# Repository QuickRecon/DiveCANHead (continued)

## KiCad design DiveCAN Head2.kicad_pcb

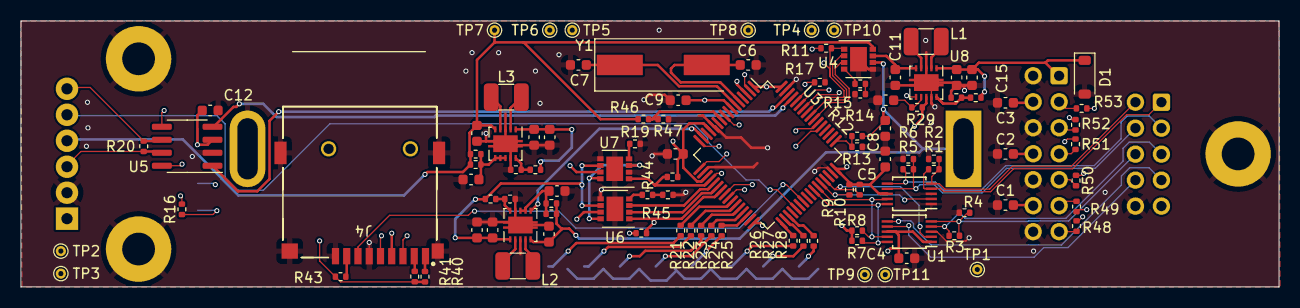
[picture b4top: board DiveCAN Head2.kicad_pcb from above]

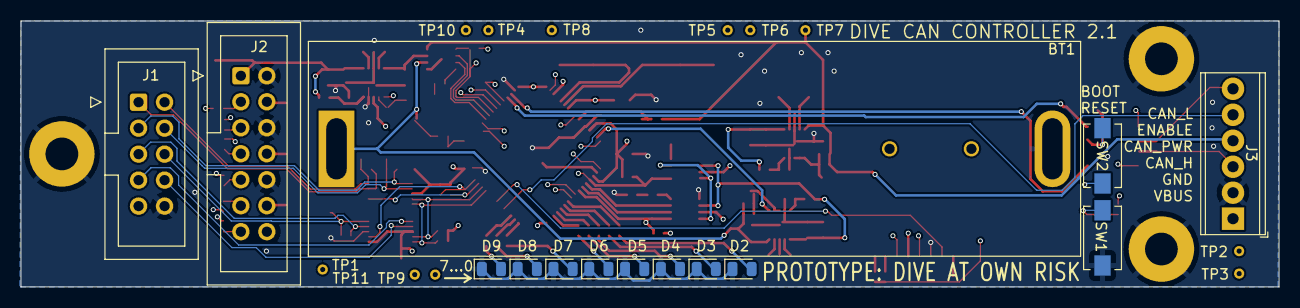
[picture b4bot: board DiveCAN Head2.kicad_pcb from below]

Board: 4 copper layers, 123.0 x 26.0 mm, 120 parts (14 on the bottom side), 94 nets.

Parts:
BT1: Battery_Cell; BatteryHolder_MPD_BH-18650-PC2
C1, C2, C3, C4, C5, C9, C10, C12, C13, C16, C19: 100n; C_0603_1608Metric
C6, C7: 20p; C_0603_1608Metric
C8, C11, C14, C15, C17, C18, C20, C21, C22, C23: 10u; C_0603_1608Metric
D1: MBR0520; D_SOD-123
D2, D3, D4, D5, D6, D7, D8, D9: LED; LED_0805_2012Metric
H1, H2, H4: MountingHole_Pad; MountingHole_3.2mm_M3_Pad
J1: Analog Connection; IDC-Header_2x05_P2.54mm_Vertical
J2: Digital Connection; IDC-Header_2x07_P2.54mm_Vertical
J3: Conn_01x06_Pin; TerminalBlock_Phoenix_MPT-0,5-6-2.54_1x06_P2.54mm_Horizontal
J4: Micro_SD_Card; CONN9_0185-02_GSW
L1, L2, L3: 2.2u; L_4x4
R1, R3, R5, R7, R8, R9, R10, R11, R12, R13, R16, R17, R18, R21, R22, R23, R24, R25, R26, R27, R28, R40, R41, R43, R45, R46, R47: 10k; R_0402_1005Metric
R2, R4, R6, R14, R15, R29, R32, R33, R36, R37, R42, R44: 200; R_0402_1005Metric
R19, R48, R49, R50, R51, R52, R53: 800; R_0402_1005Metric
R20: 560; R_0402_1005Metric
R30, R34, R38: 1M; R_0402_1005Metric
R31: 100k; R_0402_1005Metric
R35, R39: 178k; R_0402_1005Metric
SW1, SW2: RST; SW_SPST_EVQPE1
TP1: BATTERY; TestPoint_THTPad_D1.0mm_Drill0.5mm
TP2: VCC; TestPoint_THTPad_D1.0mm_Drill0.5mm
TP3: VBUS; TestPoint_THTPad_D1.0mm_Drill0.5mm
TP4: SOL_EN; TestPoint_THTPad_D1.0mm_Drill0.5mm
TP5: BAT_REG; TestPoint_THTPad_D1.0mm_Drill0.5mm
TP6: CAN_REG; TestPoint_THTPad_D1.0mm_Drill0.5mm
TP7: CAN_PWR; TestPoint_THTPad_D1.0mm_Drill0.5mm
TP8: BAT_EN; TestPoint_THTPad_D1.0mm_Drill0.5mm
TP9: BUS_STAT; TestPoint_THTPad_D1.0mm_Drill0.5mm
TP10: SOL_STAT; TestPoint_THTPad_D1.0mm_Drill0.5mm
TP11: VCC_STAT; TestPoint_THTPad_D1.0mm_Drill0.5mm
U1, U2: ADS1115IDGS; TSSOP-10_3x3mm_P0.5mm
U3: STM32L431RCTx; LQFP-64_10x10mm_P0.5mm
U4, U6, U7: TPS2115; VSON-8_3.3x3.3mm_P0.65mm_NexFET
U5: TCAN33X; SOIC-8_3.9x4.9mm_P1.27mm
U8, U9, U10: TPS63000; Texas_DRC0010J
Y1: 8MHz; Crystal_SMD_HC49-SD

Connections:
/ALRT_ADC1: R9.2, U2.2 (ALERT/RDY), U3.44 (PA11)
/ALRT_ADC2: R10.2, U1.2 (ALERT/RDY), U3.45 (PA12)
/AUX+: J1.7, U1.6 (AIN2)
/AUX-: J1.8, U1.7 (AIN3)
/BATTERY: BT1.1 (+), C8.2, C22.1, R12.2, R32.2, R33.2, TP1.1, U4.6 (IN2), U9.5 (VIN)
/BATTERY_EN: TP8.1, U3.15 (PA1), U9.6 (EN)
/BATTERY_REGULATED: C17.1, C18.1, R34.1, TP5.1, U6.6 (IN2), U7.6 (IN2), U9.1 (VOUT)
/BOOT: R17.2, SW2.1 (A), U3.60 (PH3)
/BUS_SEL1: U3.22 (PA6), U6.2 (D0)
/BUS_SEL2: U3.21 (PA5), U6.3 (D1)
/BUS_STAT: R45.2, TP9.1, U3.23 (PA7), U6.1 (STAT)
/C1+: J1.1, R1.1, U2.4 (AIN0)
/C1-: J1.2, R1.2, R2.1, U2.5 (AIN1)
/C2+: J1.3, R5.1, U2.6 (AIN2)
/C2-: J1.4, R5.2, R6.1, U2.7 (AIN3)
/C3+: J1.5, R3.1, U1.4 (AIN0)
/C3-: J1.6, R3.2, R4.1, U1.5 (AIN1)
/CAN_PWR: C23.1, J3.4, R36.2, R37.2, R46.2, TP7.1, U4.8 (IN1), U10.5 (VIN)
/CAN_REGULATED: C20.1, C21.1, R38.1, TP6.1, U6.8 (IN1), U7.3 (D1), U7.8 (IN1), U10.1 (VOUT)
/CAN_SHDN: U3.3 (PC14), U5.5 (SHDN)
/CAN_SILENT: U3.2 (PC13), U5.8 (S)
/LED_0: R21.2, U3.26 (PB0)
/LED_1: R22.2, U3.27 (PB1)
/LED_2: R23.2, U3.28 (PB2)
/LED_3: R24.2, U3.29 (PB10)
/LED_4: R25.2, U3.30 (PB11)
/LED_5: R26.2, U3.33 (PB12)
/LED_6: R27.2, U3.34 (PB13)
/LED_7: R28.2, U3.35 (PB14)
/RST: C9.2, R16.1, SW1.2 (B), U3.7 (NRST)
/SCL: R7.2, U1.10 (SCL), U2.10 (SCL), U3.42 (PA9)
/SDA: R8.2, U1.9 (SDA), U2.9 (SDA), U3.43 (PA10)
/SD_CLK: J4.5 (CLK), U3.53 (PC12)
/SD_CMD: J4.3 (CMD), U3.54 (PD2)
/SD_DAT0: J4.7 (DAT0), U3.39 (PC8)
/SOLENOID: TP4.1, U3.9 (PC1), U8.6 (EN)
/SOL_OUT: C14.1, C15.1, D1.1 (K), J2.1, R30.1, U8.1 (VOUT)
/SOL_SEL1: U3.56 (PB4), U4.2 (D0)
/SOL_SEL2: U3.55 (PB3), U4.3 (D1)
/SOL_STAT: R11.2, TP10.1, U3.57 (PB5), U4.1 (STAT)
/SSC1_RX: R52.1, U3.59 (PB7)
/SSC1_TX: R53.1, U3.58 (PB6)
/SSC2_RX: R50.1, U3.16 (PA2)
/SSC2_TX: R51.1, U3.17 (PA3)
/SSC3_RX: R48.1, U3.24 (PC4)
/SSC3_TX: R49.1, U3.25 (PC5)
/Solenoid Driver/IN: C11.2, U4.7 (OUT), U8.5 (VIN)
/VCC_STAT: R18.2, TP11.1, U3.20 (PA4), U7.1 (STAT)
/~CAN_EN: J3.5, U3.37 (PC6)
GNDREF: BT1.2 (-), C1.1, C2.1, C3.1, C4.2, C5.2, C6.1, C7.1, C8.1, C9.1, C10.2, C11.1, C12.2, C13.1, C14.2, C15.2, C16.1, C17.2, C18.2, C19.1, C20.2, C21.2, C22.2, C23.2, D1.2 (A), D2.1 (K), D3.1 (K), D4.1 (K), D5.1 (K), D6.1 (K), D7.1 (K), D8.1 (K), D9.1 (K), H1.1, H2.1, H4.1, J1.10, J2.2, J2.6, J2.10, J2.14, J3.2, J4.6 (VSS), J4.9 (SHIELD), R2.2, R4.2, R6.2, R13.1, R14.1, R17.1, R19.2, R31.2, R35.2, R39.2, R42.1, R47.1, SW1.1 (A), U1.3 (GND), U2.1 (ADDR), U2.3 (GND), U3.12 (VSSA), U3.18 (VSS), U3.31 (VSS), U3.47 (VSS), U3.63 (VSS), U4.5 (GND), U5.2 (GND), U6.5 (GND), U7.2 (D0), U7.5 (GND), U8.3 (PGND), U8.9 (GND), U8.11 (PGND), U9.3 (PGND), U9.9 (GND), U9.11 (PGND), U10.3 (PGND), U10.9 (GND), U10.11 (PGND)
unnamed: D2.2 (A), R21.1
unnamed: D3.2 (A), R22.1
unnamed: D4.2 (A), R23.1
unnamed: D5.2 (A), R24.1
unnamed: D6.2 (A), R25.1
unnamed: D7.2 (A), R26.1
unnamed: D8.2 (A), R27.1
unnamed: D9.2 (A), R28.1
unnamed: J2.3, R53.2
unnamed: J2.5, R52.2
unnamed: J2.7, R51.2
unnamed: J2.9, R50.2
unnamed: J2.11, R49.2
unnamed: J2.13, R48.2
unnamed: J3.3, R20.1, U5.7 (CANH)
unnamed: J3.6, R20.2, U5.6 (CANL)
unnamed: J4.8 (DAT1), R43.1
unnamed: J4.1 (DAT2), R40.1
unnamed: J4.2 (DAT3/CD), R41.1
unnamed: R14.2, R15.1
unnamed: R42.2, R44.1
unnamed: R12.1, R13.2, U3.49 (PA14)
unnamed: U3.61 (PB8), U5.4 (RXD)
unnamed: U3.62 (PB9), U5.1 (TXD)
unnamed: R46.1, R47.2, U3.10 (PC2)
unnamed: C6.2, U3.5 (PH0), Y1.2
unnamed: C7.2, U3.6 (PH1), Y1.1
unnamed: R15.2, U4.4 (I_LIM)
unnamed: R44.2, U6.4 (I_LIM)
unnamed: R19.1, U7.4 (I_LIM)
unnamed: R30.2, R31.1, U8.10 (FB)
unnamed: L1.2, U8.4 (L1)
unnamed: L1.1, U8.2 (L2)
unnamed: C13.2, R29.2, U8.7 (PS/SYNC)
unnamed: R34.2, R35.1, U9.10 (FB)
unnamed: L2.2, U9.4 (L1)
unnamed: L2.1, U9.2 (L2)
unnamed: C16.2, R32.1, R33.1, U9.7 (PS/SYNC), U9.8 (VINA)
unnamed: C19.2, R36.1, R37.1, U10.6 (EN), U10.7 (PS/SYNC), U10.8 (VINA)
unnamed: R38.2, R39.1, U10.10 (FB)
unnamed: L3.2, U10.4 (L1)
unnamed: L3.1, U10.2 (L2)
VBUS: C1.2, C2.2, C3.2, J1.9, J2.4, J2.8, J2.12, J3.1, J4.4 (VDD), TP3.1, U6.7 (OUT)
VCC: C4.1, C5.1, C10.1, C12.1, R7.1, R8.1, R9.1, R10.1, R11.1, R16.2, R18.1, R29.1, R40.2, R41.2, R43.2, R45.1, SW2.2 (B), TP2.1, U1.1 (ADDR), U1.8 (VDD), U2.8 (VDD), U3.1 (VBAT), U3.13 (VDDA), U3.19 (VDD), U3.32 (VDD), U3.48 (VDD), U3.64 (VDD), U5.3 (VCC), U7.7 (OUT), U8.8 (VINA)

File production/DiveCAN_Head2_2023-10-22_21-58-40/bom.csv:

Designator,Footprint,Quantity,Value,LCSC Part #
BT1,BatteryHolder_MPD_BH-18650-PC2,1,Battery_Cell,C5290176
"C1, C10, C12, C13, C16, C19, C2, C3, C4, C5, C9",0603,11,100n,C14663
"C11, C14, C15, C17, C18, C20, C21, C22, C23, C8",0603,10,10u,C19702
"C6, C7",0603,2,20p,C363552
D1,D_SOD-123,1,MBR0520,C5204745
"D2, D3, D4, D5, D6, D7, D8, D9",0805,8,LED,C84256
J2,IDC-Header_2x07_P2.54mm_Vertical,1,Digital Connection,
J3,"TerminalBlock_Phoenix_MPT-0,5-6-2.54_1x06_P2.54mm_Horizontal",1,Conn_01x06_Pin,
J4,CONN9_0185-02_GSW,1,Micro_SD_Card,C5155564
"L1, L2, L3",L_4x4,3,2.2u,C701258
"R1, R10, R11, R12, R13, R16, R17, R21, R22, R23, R24, R25, R26, R27, R28, R3, R40, R41, R43, R5, R7, R8, R9",0402,23,10k,C26083
"R14, R15, R2, R29, R32, R33, R36, R37, R4, R42, R44, R6",0402,12,200,C25087
R19,0402,1,800,C25130
R20,0402,1,560,C163460
"R30, R34, R38",0402,3,1M,C26083
R31,0402,1,100k,C140218
"R35, R39",0402,2,178k,C321342
"SW1, SW2",SW_SPST_EVQPE1,2,RST,C2915176
"U1, U2",TSSOP-10_3x3mm_P0.5mm,2,ADS1115IDGS,C37593
"U10, U8, U9",Texas_DRC0010J,3,TPS63000,C24966
U3,LQFP-64_10x10mm_P0.5mm,1,STM32L431RCTx,C92468
"U4, U6, U7",VSON-8_3.3x3.3mm_P0.65mm_NexFET,3,TPS2115,C140321
U5,SOIC-8_3.9x4.9mm_P1.27mm,1,TCAN33X,C73651
Y1,Crystal_SMD_HC49-SD,1,8MHz,C963524

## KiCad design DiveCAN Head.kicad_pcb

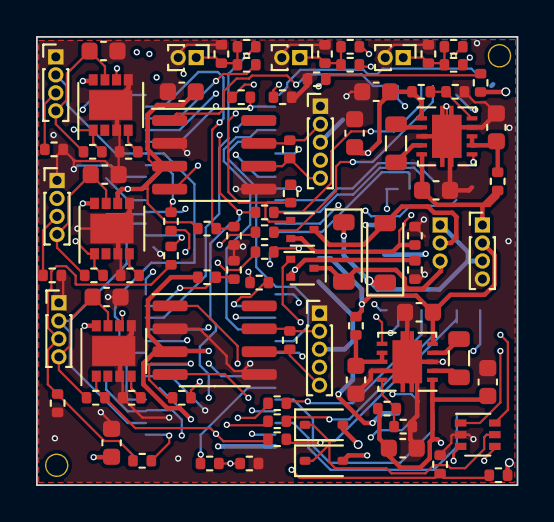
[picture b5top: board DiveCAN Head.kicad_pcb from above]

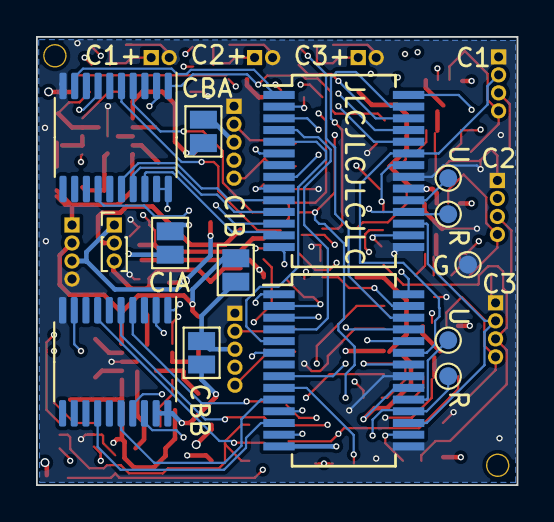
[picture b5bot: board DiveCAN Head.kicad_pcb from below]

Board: 4 copper layers, 26.7 x 24.9 mm, 104 parts (14 on the bottom side), 93 nets.

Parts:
C1, C2, C5, C6, C7, C8: 10u; C_0603_1608Metric
C3, C4, C9, C10, C11, C12, C13: 100n; C_0603_1608Metric
D1, D2: 1N5819WS; D_SOD-323
D3, D4: MBR0520; D_SOD-123
J1: POWER CONNECTION; PinHeader_1x04_P1.00mm_Vertical
J2: Solenoid out; PinHeader_1x03_P1.00mm_Vertical
J3, J4, J5: SSC1; PinHeader_1x04_P1.00mm_Vertical
J6, J7: Conn_01x05_Socket; PinHeader_1x05_P1.00mm_Vertical
J8, J9, J10: C1; PinHeader_1x02_P1.00mm_Vertical
JP1, JP2, JP3, JP4: SolderJumper-2_P1.3mm_Open_Pad1.0x1.5mm
L1, L2: 2.2u; L_0805_2012Metric
Q1, Q2: DMG1012T; SOT-523
R1, R2, R3, R30, R35: 100k; R_0402_1005Metric
R4, R5, R6, R7, R8, R9, R10, R11, R14, R15, R16, R17, R18, R19, R40, R41, R42, R43, R44, R45, R46, R47, R48: 10K; R_0402_1005Metric
R12, R21: 200; R_0402_1005Metric
R13, R22, R49, R51: 1M; R_0402_1005Metric
R20, R23: 0.5; R_0402_1005Metric
R24, R26, R28: 5K; R_0402_1005Metric
R25, R27, R29: 800; R_0402_1005Metric
R31, R36: 4k; R_0402_1005Metric
R32, R37: 4.02k; R_0402_1005Metric
R33, R38: 499k; R_0402_1005Metric
R34, R39: 560; R_0402_1005Metric
R50, R52: 178k; R_0402_1005Metric
TP1: GND; TestPoint_Pad_D1.0mm
TP2, TP4: RST; TestPoint_Pad_D1.0mm
TP3, TP5: UPDI; TestPoint_Pad_D1.0mm
U1: 74LVC2G14; SOT-363_SC-70-6
U2, U3: TPS63000; Texas_DRC0010J
U4, U5, U6: TPS2115; VSON-8_3.3x3.3mm_P0.65mm_NexFET
U7, U10: AVR32EA28; SSOP-28_5.3x10.2mm_P0.65mm
U8, U11: MCP2515-xSO; TSSOP-20_4.4x6.5mm_P0.65mm
U9, U12: TCAN330; SOIC-8_3.9x4.9mm_P1.27mm

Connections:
/BUS_A: C6.1, C8.1, C12.2, JP1.1 (A), R30.1, R51.1, U3.1 (VOUT), U4.6 (IN2), U5.6 (IN2), U6.6 (IN2), U7.14 (VDD), U7.20 (VDD), U8.19 (~RESET), U8.20 (VDD), U9.3 (VCC)
/BUS_B: C5.1, C7.1, C13.2, JP2.1 (A), R35.1, R49.1, U2.1 (VOUT), U4.8 (IN1), U5.8 (IN1), U6.8 (IN1), U10.14 (VDD), U10.20 (VDD), U11.19 (~RESET), U11.20 (VDD), U12.3 (VCC)
/BUS_SOLENOID: D3.1 (K), D4.1 (K), J1.3, J2.1, R33.2, R38.2
/C1_A: R41.1, U7.24 (PA2)
/C1_B: R42.1, U10.24 (PA2)
/C2_A: R44.1, U7.25 (PA3)
/C2_B: R45.1, U10.25 (PA3)
/C3_A: R47.1, U7.26 (PA4)
/C3_B: R48.1, U10.26 (PA4)
/CAN_A_PWR: J6.3, JP1.2 (B), JP3.2 (B)
/CAN_B_PWR: J7.3, JP2.2 (B), JP4.2 (B)
/Controller A/CLK: U7.1 (PA7), U8.9 (OSC1)
/Controller A/RST: TP2.1, U7.18 (PF6_(~RESET)), U10.8 (PD2)
/Controller A/SCL: U7.5 (PC3), U10.5 (PC3)
/Controller A/SDA: U7.4 (PC2), U10.4 (PC2)
/Controller A/SOLENOID: R12.2, U7.9 (PD3)
/Controller A/SOLENOID_RET: Q1.2 (S), R20.1, U7.28 (PA6)
/Controller A/SSC1_PWR: R9.2, U8.4 (~TX0RTS)
/Controller A/SSC1_RX: R6.2, U7.22 (PA0_(XTALHF1))
/Controller A/SSC2_PWR: R10.2, U8.5 (~TX1RTS)
/Controller A/SSC2_RX: R7.2, U7.2 (PC0)
/Controller A/SSC3_PWR: R11.2, U8.7 (~TX2RTS)
/Controller A/SSC3_RX: R8.2, U7.16 (PF0_(XTAL32K1))
/Controller A/UPDI: TP3.1, U7.19 (PF7_(UPDI))
/Controller B/CLK: U10.1 (PA7), U11.9 (OSC1)
/Controller B/RST: TP4.1, U7.8 (PD2), U10.18 (PF6_(~RESET))
/Controller B/SOLENOID: R21.2, U10.9 (PD3)
/Controller B/SOLENOID_RET: Q2.2 (S), R23.1, U10.28 (PA6)
/Controller B/SSC1_PWR: R17.2, U11.4 (~TX0RTS)
/Controller B/SSC1_RX: R14.2, U10.22 (PA0_(XTALHF1))
/Controller B/SSC2_PWR: R18.2, U11.5 (~TX1RTS)
/Controller B/SSC2_RX: R15.2, U10.2 (PC0)
/Controller B/SSC3_PWR: R19.2, U11.7 (~TX2RTS)
/Controller B/SSC3_RX: R16.2, U10.16 (PF0_(XTAL32K1))
/Controller B/UPDI: TP5.1, U10.19 (PF7_(UPDI))
/IN_A: C2.2, D1.2 (A), J1.1, JP3.1 (A), R5.1, U3.5 (VIN)
/IN_B: C1.2, D2.2 (A), J1.2, JP4.1 (A), R4.1, U2.5 (VIN)
/SSC1_PWR: R9.1, R17.1, R24.2, U4.1 (STAT)
/SSC1_RX: J3.3, R1.1, R6.1, R14.1
/SSC1_TX: J3.2, U7.23 (PA1_(XTALHF2)), U10.23 (PA1_(XTALHF2))
/SSC2_PWR: R10.1, R18.1, R26.2, U5.1 (STAT)
/SSC2_RX: J4.3, R2.1, R7.1, R15.1
/SSC2_TX: J4.2, U7.3 (PC1), U10.3 (PC1)
/SSC3_PWR: R11.1, R19.1, R28.2, U6.1 (STAT)
/SSC3_RX: J5.3, R3.1, R8.1, R16.1
/SSC3_TX: J5.2, U7.17 (PF1_(XTAP32K2)), U10.17 (PF1_(XTAP32K2))
/~EN_A: J6.4, U1.1
/~EN_B: J7.4, U1.3
GNDREF: C1.1, C2.1, C3.1, C4.1, C5.2, C6.2, C7.2, C8.2, C9.2, C10.2, C11.2, C12.1, C13.1, J1.4, J3.1, J4.1, J5.1, J6.1, J7.1, J8.2, J9.2, J10.2, R1.2, R2.2, R3.2, R13.2, R20.2, R22.2, R23.2, R25.2, R27.2, R29.2, R31.2, R32.2, R36.2, R37.2, R40.1, R43.1, R46.1, R50.2, R52.2, TP1.1, U1.2 (GND), U2.3 (PGND), U2.9 (GND), U2.11 (PGND), U3.3 (PGND), U3.9 (GND), U3.11 (PGND), U4.3 (D1), U4.5 (GND), U5.3 (D1), U5.5 (GND), U6.3 (D1), U6.5 (GND), U7.15 (GND), U7.21 (GND), U8.10 (VSS), U9.2 (GND), U9.5 (SHDN), U10.15 (GND), U10.21 (GND), U11.10 (VSS), U12.2 (GND), U12.5 (SHDN)
unnamed: D1.1 (K), D2.1 (K), U1.5 (VCC)
unnamed: D3.2 (A), J2.2, Q1.3 (D)
unnamed: D4.2 (A), J2.3, Q2.3 (D)
unnamed: C9.1, J3.4, R24.1, U4.7 (OUT)
unnamed: C10.1, J4.4, R26.1, U5.7 (OUT)
unnamed: C11.1, J5.4, R28.1, U6.7 (OUT)
unnamed: J6.2, R34.1, U9.7 (CANH)
unnamed: J6.5, R34.2, U9.6 (CANL)
unnamed: J7.2, R39.1, U12.7 (CANH)
unnamed: J7.5, R39.2, U12.6 (CANL)
unnamed: J8.1, R40.2, R41.2, R42.2
unnamed: J9.1, R43.2, R44.2, R45.2
unnamed: J10.1, R46.2, R47.2, R48.2
unnamed: Q1.1 (G), R12.1, R13.1
unnamed: Q2.1 (G), R21.1, R22.1
unnamed: U1.4, U2.6 (EN)
unnamed: R49.2, R50.1, U2.10 (FB)
unnamed: L1.2, U2.4 (L1)
unnamed: L1.1, U2.2 (L2)
unnamed: C3.2, R4.2, U2.7 (PS/SYNC), U2.8 (VINA)
unnamed: U1.6, U3.6 (EN)
unnamed: R51.2, R52.1, U3.10 (FB)
unnamed: L2.2, U3.4 (L1)
unnamed: L2.1, U3.2 (L2)
unnamed: C4.2, R5.2, U3.7 (PS/SYNC), U3.8 (VINA)
unnamed: R25.1, U4.4 (I_LIM)
unnamed: R27.1, U5.4 (I_LIM)
unnamed: R29.1, U6.4 (I_LIM)
unnamed: R30.2, R31.1, U7.27 (PA5)
unnamed: R32.1, R33.1, U7.6 (PD0)
unnamed: U7.10 (PD4), U8.16 (SI)
unnamed: U7.11 (PD5), U8.17 (SO)
unnamed: U7.12 (PD6), U8.14 (SCK)
unnamed: U7.13 (PD7), U8.18 (~CS)
unnamed: U8.2 (RXCAN), U9.4 (RXD)
unnamed: U8.1 (TXCAN), U9.1 (TXD)
unnamed: R35.2, R36.1, U10.27 (PA5)
unnamed: R37.1, R38.1, U10.6 (PD0)
unnamed: U10.10 (PD4), U11.16 (SI)
unnamed: U10.11 (PD5), U11.17 (SO)
unnamed: U10.12 (PD6), U11.14 (SCK)
unnamed: U10.13 (PD7), U11.18 (~CS)
unnamed: U11.2 (RXCAN), U12.4 (RXD)
unnamed: U11.1 (TXCAN), U12.1 (TXD)

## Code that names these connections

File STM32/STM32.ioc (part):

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Mcu.Name=STM32L431R(B-C)Tx
Mcu.Package=LQFP64
Mcu.UserName=STM32L431RCTx
PA0.GPIOParameters=GPIO_Label
PA0.GPIO_Label=VBUS_V
PA0.Signal=ADCx_IN5
PA1.GPIOParameters=GPIO_Label
PA1.GPIO_Label=BATTERY_EN
PA1.Signal=GPIO_Output
PA10.Mode=I2C
PA10.Signal=I2C1_SDA
PA11.GPIOParameters=GPIO_PuPd,GPIO_Label,GPIO_ModeDefaultEXTI
PA11.GPIO_Label=ADC1_ALERT
PA11.GPIO_ModeDefaultEXTI=GPIO_MODE_IT_FALLING
PA11.GPIO_PuPd=GPIO_PULLUP
PA11.Signal=GPXTI11
PA12.GPIOParameters=GPIO_PuPd,GPIO_Label,GPIO_ModeDefaultEXTI
PA12.GPIO_Label=ADC2_ALERT
PA12.GPIO_ModeDefaultEXTI=GPIO_MODE_IT_FALLING
PA12.GPIO_PuPd=GPIO_PULLUP
PA12.Signal=GPXTI12
PA13\ (JTMS-SWDIO).Mode=Trace_Asynchronous_SW
PA13\ (JTMS-SWDIO).Signal=SYS_JTMS-SWDIO
PA14\ (JTCK-SWCLK).Mode=Trace_Asynchronous_SW
PA14\ (JTCK-SWCLK).Signal=SYS_JTCK-SWCLK
PA15\ (JTDI).GPIOParameters=GPIO_Label
PA15\ (JTDI).GPIO_Label=GPIO_B
PA15\ (JTDI).Signal=GPIO_Output
PA2.Mode=Asynchronous
PA2.Signal=USART2_TX
PA3.Mode=Asynchronous
PA3.Signal=USART2_RX
PA4.GPIOParameters=GPIO_PuPd,GPIO_Label
PA4.GPIO_Label=VCC_STAT
PA4.GPIO_PuPd=GPIO_PULLUP
PA4.Signal=GPIO_Input
PA5.GPIOParameters=GPIO_Label
PA5.GPIO_Label=BUS_SEL2
PA5.Signal=GPIO_Output
PA6.GPIOParameters=GPIO_Label
PA6.GPIO_Label=BUS_SEL1
PA6.Signal=GPIO_Output
PA7.GPIOParameters=GPIO_PuPd,GPIO_Label
PA7.GPIO_Label=BUS_STAT
PA7.GPIO_PuPd=GPIO_PULLUP
PA7.Signal=GPIO_Input
PA8.GPIOParameters=GPIO_Label
PA8.GPIO_Label=PWM_1
PA8.Signal=S_TIM1_CH1
PA9.Mode=I2C
PA9.Signal=I2C1_SCL
PB0.GPIOParameters=PinState,GPIO_Label
PB0.GPIO_Label=LED0
PB0.PinState=GPIO_PIN_RESET
PB0.Signal=GPIO_Output
PB1.GPIOParameters=PinState,GPIO_Label
PB1.GPIO_Label=LED1
PB1.PinState=GPIO_PIN_RESET
PB1.Signal=GPIO_Output
PB10.GPIOParameters=PinState,GPIO_Label
PB10.GPIO_Label=LED3
PB10.PinState=GPIO_PIN_RESET
PB10.Signal=GPIO_Output
PB11.GPIOParameters=PinState,GPIO_Label
PB11.GPIO_Label=LED4
PB11.PinState=GPIO_PIN_RESET
PB11.Signal=GPIO_Output
PB12.GPIOParameters=PinState,GPIO_Label
PB12.GPIO_Label=LED5
PB12.PinState=GPIO_PIN_RESET
PB12.Signal=GPIO_Output
PB13.GPIOParameters=PinState,GPIO_Label
PB13.GPIO_Label=LED6
PB13.PinState=GPIO_PIN_RESET
PB13.Signal=GPIO_Output
PB14.GPIOParameters=PinState,GPIO_Label
PB14.GPIO_Label=LED7
PB14.PinState=GPIO_PIN_RESET
PB14.Signal=GPIO_Output
PB15.Signal=S_TIM15_CH2
PB2.GPIOParameters=PinState,GPIO_Label
PB2.GPIO_Label=LED2
PB2.PinState=GPIO_PIN_RESET
PB2.Signal=GPIO_Output
PB3\ (JTDO-TRACESWO).Mode=Trace_Asynchronous_SW
PB3\ (JTDO-TRACESWO).Signal=SYS_JTDO-SWO
PB4\ (NJTRST).GPIOParameters=GPIO_Label
PB4\ (NJTRST).GPIO_Label=SOL_DIS_CAN
PB4\ (NJTRST).Signal=GPIO_Output
PB5.GPIOParameters=GPIO_PuPd,GPIO_Label
PB5.GPIO_Label=SOL_STAT
PB5.GPIO_PuPd=GPIO_PULLUP
PB5.Signal=GPIO_Input
PB6.Mode=Asynchronous
PB6.Signal=USART1_TX
PB7.Mode=Asynchronous
PB7.Signal=USART1_RX
PB8.Mode=CAN_Activate
PB8.Signal=CAN1_RX
PB9.Mode=CAN_Activate
PB9.Signal=CAN1_TX
PC0.GPIOParameters=GPIO_Label
PC0.GPIO_Label=VER_DET_1
PC0.Signal=GPIO_Input
PC1.GPIOParameters=GPIO_Label
PC1.GPIO_Label=SOLENOID
PC1.Signal=GPIO_Output
PC10.GPIOParameters=GPIO_Label
PC10.GPIO_Label=VER_DET_3
PC10.Signal=GPIO_Input
PC11.GPIOParameters=GPIO_Label
PC11.GPIO_Label=SOL_DIS_BATT
PC11.Signal=GPIO_Output
PC12.GPIOParameters=GPIO_PuPd
PC12.GPIO_PuPd=GPIO_NOPULL
PC12.Mode=SD_1_bit
PC12.Signal=SDMMC1_CK
PC13.GPIOParameters=GPIO_PuPd,GPIO_Label
PC13.GPIO_Label=CAN_EN
PC13.GPIO_PuPd=GPIO_NOPULL
PC13.Signal=GPIO_Input
PC14-OSC32_IN\ (PC14).GPIOParameters=GPIO_Label
PC14-OSC32_IN\ (PC14).GPIO_Label=CAN_SHDN
PC14-OSC32_IN\ (PC14).Signal=GPIO_Output
PC15-OSC32_OUT\ (PC15).GPIOParameters=GPIO_Label
PC15-OSC32_OUT\ (PC15).GPIO_Label=CAN_SILENT
PC15-OSC32_OUT\ (PC15).Signal=GPIO_Input
PC2.GPIOParameters=GPIO_Label
PC2.GPIO_Label=CAN_V
PC2.Signal=ADCx_IN3
PC3.GPIOParameters=GPIO_Label
PC3.GPIO_Label=BATT_V
PC3.Signal=ADCx_IN4
PC4.Mode=Asynchronous
PC4.Signal=USART3_TX
PC5.Mode=Asynchronous
PC5.Signal=USART3_RX
PC6.GPIOParameters=GPIO_PuPd,GPIO_Label
PC6.GPIO_Label=SD_DET
PC6.GPIO_PuPd=GPIO_PULLDOWN
PC6.Signal=GPIO_Input
PC7.GPIOParameters=GPIO_Label
PC7.GPIO_Label=GPIO_A
PC7.Signal=GPIO_Output
PC8.GPIOParameters=GPIO_PuPd
PC8.GPIO_PuPd=GPIO_PULLUP
PC8.Mode=SD_1_bit
PC8.Signal=SDMMC1_D0
PC9.GPIOParameters=GPIO_Label
PC9.GPIO_Label=VER_DET_2
PC9.Signal=GPIO_Input
PD2.GPIOParameters=GPIO_PuPd
PD2.GPIO_PuPd=GPIO_PULLUP
PD2.Mode=SD_1_bit
PD2.Signal=SDMMC1_CMD
PH0-OSC_IN\ (PH0).Mode=HSE-External-Oscillator
PH0-OSC_IN\ (PH0).Signal=RCC_OSC_IN
PH1-OSC_OUT\ (PH1).Mode=HSE-External-Oscillator
PH1-OSC_OUT\ (PH1).Signal=RCC_OSC_OUT
RCC.HSE_VALUE=8000000
RCC.SYSCLKFreq_VALUE=12000000
RCC.SYSCLKSource=RCC_SYSCLKSOURCE_PLLCLK
board=custom

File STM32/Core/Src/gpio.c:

/* USER CODE BEGIN Header */
/**
  ******************************************************************************
  * @file    gpio.c
  * @brief   This file provides code for the configuration
  *          of all used GPIO pins.
  ******************************************************************************
  * @attention
  *
  * Copyright (c) 2023 STMicroelectronics.
  * All rights reserved.
  *
  * This software is licensed under terms that can be found in the LICENSE file
  * in the root directory of this software component.
  * If no LICENSE file comes with this software, it is provided AS-IS.
  *
  ******************************************************************************
  */
/* USER CODE END Header */

/* Includes ------------------------------------------------------------------*/
#include "gpio.h"

/* USER CODE BEGIN 0 */

/* USER CODE END 0 */

/*----------------------------------------------------------------------------*/
/* Configure GPIO                                                             */
/*----------------------------------------------------------------------------*/
/* USER CODE BEGIN 1 */

/* USER CODE END 1 */

/** Configure pins as
        * Analog
        * Input
        * Output
        * EVENT_OUT
        * EXTI
        * Free pins are configured automatically as Analog (this feature is enabled through
        * the Code Generation settings)
*/
void MX_GPIO_Init(void)
{

  GPIO_InitTypeDef GPIO_InitStruct = {0};

  /* GPIO Ports Clock Enable */
  __HAL_RCC_GPIOC_CLK_ENABLE();
  __HAL_RCC_GPIOH_CLK_ENABLE();
  __HAL_RCC_GPIOA_CLK_ENABLE();
  __HAL_RCC_GPIOB_CLK_ENABLE();
  __HAL_RCC_GPIOD_CLK_ENABLE();

  /*Configure GPIO pin Output Level */
  HAL_GPIO_WritePin(GPIOC, CAN_SILENT_Pin|CAN_SHDN_Pin|SOLENOID_Pin, GPIO_PIN_RESET);

  /*Configure GPIO pin Output Level */
  HAL_GPIO_WritePin(GPIOA, BATTERY_EN_Pin|BUS_SEL2_Pin|BUS_SEL1_Pin, GPIO_PIN_RESET);

  /*Configure GPIO pin Output Level */
  HAL_GPIO_WritePin(GPIOB, LED0_Pin|LED1_Pin|LED2_Pin|LED3_Pin
                          |LED4_Pin|LED5_Pin|LED6_Pin|LED7_Pin
                          |SOL_SEL2_Pin|SOL_SEL1_Pin, GPIO_PIN_RESET);

  /*Configure GPIO pins : PCPin PCPin PCPin */
  GPIO_InitStruct.Pin = CAN_SILENT_Pin|CAN_SHDN_Pin|SOLENOID_Pin;
  GPIO_InitStruct.Mode = GPIO_MODE_OUTPUT_PP;
  GPIO_InitStruct.Pull = GPIO_NOPULL;
  GPIO_InitStruct.Speed = GPIO_SPEED_FREQ_LOW;
  HAL_GPIO_Init(GPIOC, &GPIO_InitStruct);

  /*Configure GPIO pins : PC15 PC2 PC3 PC6
                           PC7 PC9 PC10 */
  GPIO_InitStruct.Pin = GPIO_PIN_15|GPIO_PIN_2|GPIO_PIN_3|GPIO_PIN_6
                          |GPIO_PIN_7|GPIO_PIN_9|GPIO_PIN_10;
  GPIO_InitStruct.Mode = GPIO_MODE_ANALOG;
  GPIO_InitStruct.Pull = GPIO_NOPULL;
  HAL_GPIO_Init(GPIOC, &GPIO_InitStruct);

  /*Configure GPIO pins : PCPin PCPin */
  GPIO_InitStruct.Pin = MOCK_SD_DETECT_Pin|CAN_EN_Pin;
  GPIO_InitStruct.Mode = GPIO_MODE_INPUT;
  GPIO_InitStruct.Pull = GPIO_NOPULL;
  HAL_GPIO_Init(GPIOC, &GPIO_InitStruct);

  /*Configure GPIO pins : PAPin PAPin PAPin */
  GPIO_InitStruct.Pin = BATTERY_EN_Pin|BUS_SEL2_Pin|BUS_SEL1_Pin;
  GPIO_InitStruct.Mode = GPIO_MODE_OUTPUT_PP;
  GPIO_InitStruct.Pull = GPIO_NOPULL;
  GPIO_InitStruct.Speed = GPIO_SPEED_FREQ_LOW;
  HAL_GPIO_Init(GPIOA, &GPIO_InitStruct);

  /*Configure GPIO pins : PAPin PAPin PAPin */
  GPIO_InitStruct.Pin = VCC_STAT_Pin|BUS_STAT_Pin|BATTERY_Pin;
  GPIO_InitStruct.Mode = GPIO_MODE_INPUT;
  GPIO_InitStruct.Pull = GPIO_NOPULL;
  HAL_GPIO_Init(GPIOA, &GPIO_InitStruct);

  /*Configure GPIO pins : PBPin PBPin PBPin PBPin
                           PBPin PBPin PBPin PBPin
                           PBPin PBPin */
  GPIO_InitStruct.Pin = LED0_Pin|LED1_Pin|LED2_Pin|LED3_Pin
                          |LED4_Pin|LED5_Pin|LED6_Pin|LED7_Pin
                          |SOL_SEL2_Pin|SOL_SEL1_Pin;
  GPIO_InitStruct.Mode = GPIO_MODE_OUTPUT_PP;
  GPIO_InitStruct.Pull = GPIO_NOPULL;
  GPIO_InitStruct.Speed = GPIO_SPEED_FREQ_LOW;
  HAL_GPIO_Init(GPIOB, &GPIO_InitStruct);

  /*Configure GPIO pin : PB15 */
  GPIO_InitStruct.Pin = GPIO_PIN_15;
  GPIO_InitStruct.Mode = GPIO_MODE_ANALOG;
  GPIO_InitStruct.Pull = GPIO_NOPULL;
  HAL_GPIO_Init(GPIOB, &GPIO_InitStruct);

  /*Configure GPIO pins : PA8 PA13 PA15 */
  GPIO_InitStruct.Pin = GPIO_PIN_8|GPIO_PIN_13|GPIO_PIN_15;
  GPIO_InitStruct.Mode = GPIO_MODE_ANALOG;
  GPIO_InitStruct.Pull = GPIO_NOPULL;
  HAL_GPIO_Init(GPIOA, &GPIO_InitStruct);

  /*Configure GPIO pins : PAPin PAPin */
  GPIO_InitStruct.Pin = ADC1_ALERT_Pin|ADC2_ALERT_Pin;
  GPIO_InitStruct.Mode = GPIO_MODE_IT_FALLING;
  GPIO_InitStruct.Pull = GPIO_NOPULL;
  HAL_GPIO_Init(GPIOA, &GPIO_InitStruct);

  /*Configure GPIO pin : PtPin */
  GPIO_InitStruct.Pin = SOL_STAT_Pin;
  GPIO_InitStruct.Mode = GPIO_MODE_INPUT;
  GPIO_InitStruct.Pull = GPIO_NOPULL;
  HAL_GPIO_Init(SOL_STAT_GPIO_Port, &GPIO_InitStruct);

  /*Configure GPIO pin : PH3 */
  GPIO_InitStruct.Pin = GPIO_PIN_3;
  GPIO_InitStruct.Mode = GPIO_MODE_ANALOG;
  GPIO_InitStruct.Pull = GPIO_NOPULL;
  HAL_GPIO_Init(GPIOH, &GPIO_InitStruct);

}

/* USER CODE BEGIN 2 */

/* USER CODE END 2 */

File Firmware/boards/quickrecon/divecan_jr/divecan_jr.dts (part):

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
	/* ---- Power subsystem ----
	 * Jr: single battery source, VBUS on/off only.
	 * battery_en (PA1) controls the VBUS regulator.
	 * Battery voltage sensed on ADC1 channel 4 (PC3) through 7.25x divider.
	 * VCC monitored via internal VBAT sensor (shared regulator with VBUS).
	 */
	vbus_reg: vbus-regulator {
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		vcc-sense = <&vbat>;
		/* Shared active-low enable/wake line. Firmware samples it as an
		 * input after WKUP2 wake, then holds it low until shutdown. */
		can-enable-gpios = <&gpioc 13 GPIO_ACTIVE_LOW>;
		can-shutdown-gpios = <&gpioc 14 GPIO_ACTIVE_HIGH>;
		/* CAN transceiver silent/Rs line. Driven low (normal mode) at
		 * init; asserted high (silent) going into shutdown. Owned as an
		 * output — not a passive input — so a warm start reliably clears
		 * silent mode. See power_management.c. */
		can-silent-gpios = <&gpioc 15 GPIO_ACTIVE_HIGH>;
	};
};

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
/* ---- I2C1 — ADS1115 external ADCs ----
 * Two devices: 0x48 (cells 1+2), 0x49 (cell 3 + aux)
 * PA9 = SCL, PA10 = SDA
 *
 * Analog cell -> ADC channel distribution lives here in DT (consumed by
 * src/oxygen_cell_analog.c via the zephyr,user io-channels list below), NOT in
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	pinctrl-0 = <&i2c1_scl_pa9 &i2c1_sda_pa10>;
	pinctrl-names = "default";
	clock-frequency = <I2C_BITRATE_STANDARD>;
	/* Recovery pins for i2c_recover_bus(): same PA9/PA10 lines, only ever
	 * driven (as open-drain GPIO) while CONFIG_I2C_STM32_BUS_RECOVERY is set
	 * and a recovery is in progress; pinctrl owns them otherwise. Required on
	 * the Poseidon variant. The public recovery operation is used only after
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		#address-cells = <1>;
		#size-cells = <0>;
		#io-channel-cells = <1>;
		/* ALRT_ADC1 -> PA11 is wired for a conversion-ready IRQ, but the data-ready
		 * interrupt path is NOT yet enabled: with no external pull-up on the open-drain
		 * ALERT/RDY, the weak (~40k) STM32 internal pull-up couldn't reconstruct the
		 * brief (~8us) RDY pulse, so reads stalled (all cells -> 0). Needs scope bring-up
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		#address-cells = <1>;
		#size-cells = <0>;
		#io-channel-cells = <1>;
		/* ALRT_ADC2 -> PA12 wired for conversion-ready IRQ; NOT enabled yet (see @48 —
		 * needs pull-up/scope bring-up). Polling path in use.
		 *   alert-rdy-gpios = <&gpioa 12 (GPIO_ACTIVE_LOW | GPIO_PULL_UP)>; */

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 * needed — if so, use the swapped pinctrl variants.
 */

/* Cell 1: PB6 (TX), PB7 (RX) — no swap */
&usart1 {
	pinctrl-0 = <&usart1_tx_pb6 &usart1_rx_pb7>;
	pinctrl-names = "default";
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	status = "okay";
};

/* Cell 2: PA2 (TX), PA3 (RX). JR+ Rev2 wires USART2 with TX/RX swapped
 * (ADVFEATURE_SWAP_ENABLE in the Rev2 .ioc); verified empirically on the rig
 * 2026-06-23 — cell2 only polls its CellSim with the swap applied. */
&usart2 {
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	status = "okay";
};

/* Cell 3: PC4 (TX), PC5 (RX). JR+ Rev2 wires USART3 with TX/RX swapped too
 * (USART1 is NOT swapped). See the usart2 note above. */
&usart3 {
	pinctrl-0 = <&usart3_tx_pc4 &usart3_rx_pc5>;
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};

/* ---- SPI2 — Winbond W25Q512JV external flash ----
 * PB13 = SCK, PB14 = MISO, PB15 = MOSI, PB11 = CS
 */
&spi2 {
	pinctrl-0 = <&spi2_sck_pb13 &spi2_miso_pb14 &spi2_mosi_pb15>;
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
/* ---- TIM7 — solenoid deadman timer ----
 * One-shot hardware counter. When the alarm fires (ISR),
 * all solenoid GPIOs are forced low regardless of app state.
 *
 * Prescaler tuning (PSC=7999 → divider=8000 → 100 µs/tick) gives a
 * 16-bit max one-shot of 65535 × 100 µs = 6.55 s. The driver clamp
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};

/* ---- Internal ADC — voltage monitoring ----
 * PA0 = IN5 (VBUS_V), PC2 = IN3 (CAN_V), PC3 = IN4 (BATT_V)
 * Plus internal VREFINT and VBAT channels.
 */
&adc1 {
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
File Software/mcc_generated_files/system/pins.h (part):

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
/**
 * @ingroup  pinsdriver
 * @brief Default Interrupt Handler for SSC2_TX pin. 
 *        This is a predefined interrupt handler to be used together with the SSC2_TX_SetInterruptHandler() method.
 *        This handler is called every time the SSC2_TX ISR is executed. 
 * @pre PIN_MANAGER_Initialize() has been called at least once
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
/**
 * @ingroup  pinsdriver
 * @brief Interrupt Handler Setter for SSC2_TX pin input-sense-config functionality.
 *        Allows selecting an interrupt handler for SSC2_TX at application runtime
 * @pre PIN_MANAGER_Initialize() has been called at least once
 * @param InterruptHandler function pointer.
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
/**
 * @ingroup  pinsdriver
 * @brief Default Interrupt Handler for SSC2_RX pin. 
 *        This is a predefined interrupt handler to be used together with the SSC2_RX_SetInterruptHandler() method.
 *        This handler is called every time the SSC2_RX ISR is executed. 
 * @pre PIN_MANAGER_Initialize() has been called at least once
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
/**
 * @ingroup  pinsdriver
 * @brief Interrupt Handler Setter for SSC2_RX pin input-sense-config functionality.
 *        Allows selecting an interrupt handler for SSC2_RX at application runtime
 * @pre PIN_MANAGER_Initialize() has been called at least once
 * @param InterruptHandler function pointer.
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
/**
 * @ingroup  pinsdriver
 * @brief Default Interrupt Handler for SSC3_TX pin. 
 *        This is a predefined interrupt handler to be used together with the SSC3_TX_SetInterruptHandler() method.
 *        This handler is called every time the SSC3_TX ISR is executed. 
 * @pre PIN_MANAGER_Initialize() has been called at least once
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
/**
 * @ingroup  pinsdriver
 * @brief Interrupt Handler Setter for SSC3_TX pin input-sense-config functionality.
 *        Allows selecting an interrupt handler for SSC3_TX at application runtime
 * @pre PIN_MANAGER_Initialize() has been called at least once
 * @param InterruptHandler function pointer.
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
/**
 * @ingroup  pinsdriver
 * @brief Default Interrupt Handler for SSC3_RX pin. 
 *        This is a predefined interrupt handler to be used together with the SSC3_RX_SetInterruptHandler() method.
 *        This handler is called every time the SSC3_RX ISR is executed. 
 * @pre PIN_MANAGER_Initialize() has been called at least once
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
/**
 * @ingroup  pinsdriver
 * @brief Interrupt Handler Setter for SSC3_RX pin input-sense-config functionality.
 *        Allows selecting an interrupt handler for SSC3_RX at application runtime
 * @pre PIN_MANAGER_Initialize() has been called at least once
 * @param InterruptHandler function pointer.
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
/**
 * @ingroup  pinsdriver
 * @brief Default Interrupt Handler for SSC1_TX pin. 
 *        This is a predefined interrupt handler to be used together with the SSC1_TX_SetInterruptHandler() method.
 *        This handler is called every time the SSC1_TX ISR is executed. 
 * @pre PIN_MANAGER_Initialize() has been called at least once
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
/**
 * @ingroup  pinsdriver
 * @brief Interrupt Handler Setter for SSC1_TX pin input-sense-config functionality.
 *        Allows selecting an interrupt handler for SSC1_TX at application runtime
 * @pre PIN_MANAGER_Initialize() has been called at least once
 * @param InterruptHandler function pointer.
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
/**
 * @ingroup  pinsdriver
 * @brief Default Interrupt Handler for SSC1_RX pin. 
 *        This is a predefined interrupt handler to be used together with the SSC1_RX_SetInterruptHandler() method.
 *        This handler is called every time the SSC1_RX ISR is executed. 
 * @pre PIN_MANAGER_Initialize() has been called at least once
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
/**
 * @ingroup  pinsdriver
 * @brief Interrupt Handler Setter for SSC1_RX pin input-sense-config functionality.
 *        Allows selecting an interrupt handler for SSC1_RX at application runtime
 * @pre PIN_MANAGER_Initialize() has been called at least once
 * @param InterruptHandler function pointer.
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
/**
 * @ingroup  pinsdriver
 * @brief Default Interrupt Handler for SOL_OUT pin. 
 *        This is a predefined interrupt handler to be used together with the SOL_OUT_SetInterruptHandler() method.
 *        This handler is called every time the SOL_OUT ISR is executed. 
 * @pre PIN_MANAGER_Initialize() has been called at least once
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
/**
 * @ingroup  pinsdriver
 * @brief Interrupt Handler Setter for SOL_OUT pin input-sense-config functionality.
 *        Allows selecting an interrupt handler for SOL_OUT at application runtime
 * @pre PIN_MANAGER_Initialize() has been called at least once
 * @param InterruptHandler function pointer.
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
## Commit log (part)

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2025-07-11 Patching up config for MK15 release
2025-07-14 Board Revisions
2025-09-13 Ensure the Jr Board is tracked in git
2025-09-13 Fix solenoid power distribution to prevent brownouts
2025-11-14 Jr 1.1 board revision
2025-11-14 Add archive of released firmware blobs
2025-11-15 Set up calibration of digital cells
2025-11-16 Write a list of known bugs from recent field testing
2025-11-16 Add new voting tests to catch an error case when one cell is very far away from the rest
2025-11-16 Implement new voting algorithm which better handles edge cases
2025-11-16 Enable additional runtime protections
2025-11-17 Refactor solenoid method to clear a linter warning
2025-11-17 Add check to see if the bus is actually on once we've booted up, to prevent spurious power-ons
2025-11-17 Update cpputest
2025-11-17 Add method to read input VCC
2025-11-27 Reduce resend timeout to 1 second in O2S cell
2025-11-27 Rename timeouts to be self-consistent
2025-12-06 Adjust O2S timeout
2025-12-06 Adjust stack sizes based on new observations
2025-12-06 Calibrations always roll back calibration coeffeicients on fail
2025-12-06 Update HAL and format docs
2025-12-06 Change the bus active detection on boot to more reliably detect a dodge connection
2025-12-06 Deal with a few low-hanging fruit warnings
2025-12-06 Add a check to not write to the flash if we think we're in an undervolted state
2025-12-06 Update jobs list
2025-12-06 Fix unneeded bool literal
2025-12-08 Update shitlist with results from test dive
2025-12-09 Change small float to EPS const
2025-12-09 Add an additional compiler warning to track stack increase
2025-12-09 Ensure we keep tripping the solenoid on to prevent it getting switched off by the PID loop
2025-12-11 Add more logging to O2S
2025-12-11 Reset fatal error code on clean shutdown
2025-12-11 Log if resetting the fatal error fails
2025-12-11 Add discovered divecan messages, add diving start log, reorder DiveCAN case to match the ID order
2025-12-11 Ensure control loops recognize a failed consensus
2025-12-11 Add additional checking to handle really split-brained scenarios while still reporting sensible information
2025-12-11 Ensure consistent behavior in a vote-fail scenario
2025-12-11 Fix incorrect dive numbering
2025-12-15 Comment out currently unreliable voltage check
2025-12-15 Reset default config to jr
2026-01-01 remove coverage information
2026-01-01 Add tests to define current menu behavior
2026-01-01 Initial UDS implementation
2026-01-01 Add uds on top of isotp
2026-01-01 Add integrations for UDS
2026-01-01 Fix tests
2026-01-01 Add settings USD impl
2026-01-02 Memoy upload
2026-01-02 Stub writing to flash
2026-01-06 isoTP using polling rather than callbacks
2026-01-06 ISO TP working on handset
2026-01-06 Initial clauding
2026-01-06 Revert "ISO TP working on handset"
    This reverts commit 8dc08cde6ed83958dc5c02afdcb3ef60288fd922.
2026-01-06 Park some webdev stuff for now
2026-01-06 Remove legacy crap that was hiding actual issues
2026-01-06 Update option bytes to ensure the device boots into the app
2026-01-06 remove legacy menu system and move poling of isotp to end of can msg processing
2026-01-06 More working
2026-01-07 Get digits working
2026-01-07 Get commits to show
2026-01-26 Fix failed calibration due to EPS
2026-01-26 Upgrade cable retainer to stay better attached
2026-01-26 update requirements
2026-01-26 Get writing to work
2026-01-26 Get UDS over bt working
2026-01-26 Remove uneeded ISOTP junk
2026-01-26 Fix rx timing bug
2026-01-26 Rework to investigate multiple devices on bus
2026-01-26 Try to get settings enumeration to work
2026-01-26 Get basic printing over uds to work
2026-01-26 Get menu to work
2026-01-26 Implement patch for weird space requirement and speed up fetching
2026-01-26 Add logging of cell stuff to uds
2026-01-26 Formatter pass and enable CAN autoretransmit
2026-01-26 Move Events onto a different channel
2026-01-26 Add priority to state queue, update ui
2026-01-26 Create diagnostics page
2026-01-26 Set debug level and fix old timestamps
2026-01-28 Intrim debug commit
2026-01-28 Fix blocking CAN
2026-01-29 Get a state vector based solution working
2026-01-29 try and do some performance enhancement
2026-01-29 Change to using DIDs rather than a state vector
2026-01-29 Try and do a bit of speeding up
2026-01-29 Adjust the order of operations to run things a bit quicker
2026-01-29 Fix menu offset issues,
2026-01-29 Add power data to the DIDs
2026-01-29 Include cell status in information
2026-01-29 Get claude to give itself some better context to play in
2026-01-29 Set up config decoding
2026-01-29 Have stale values show as stale
2026-01-29 Fix incorrect message length when using small messages
2026-01-29 Fix low battery alarm to work correctly based on new spec data
2026-01-29 Print information on successful config save
2026-01-29 Do some styling
2026-01-29 Ensure millis, setpoint, PPO2 come through the UDS correctly
2026-01-29 Add calibration pipeline
2026-01-30 Strip out unused UDS infrastructure
2026-01-30 Have log always broadcast (reduce amount of tracked state)
2026-01-30 Strip out the log stream enable
2026-01-30 Ensure comment consistency
2026-01-30 Ensure claude can see sonarqube
2026-01-30 Use typedefs
2026-01-30 Fix error case duplication
2026-01-30 Avoid magic numbers
2026-01-30 Operator parens
2026-01-30 More magic number removal
2026-01-30 Add a bunch of error handling
2026-01-30 Bring things into naming compliance
2026-01-30 Code cleanup pass, fix rentrant logging bug
2026-01-30 Extract state into static funcs
2026-01-30 Simplify functions
2026-01-30 Eliminate multiple returns
2026-01-30 Extract and simplify some functions
2026-01-30 Web cleanup pass
2026-01-30 Update JS more
2026-01-30 Another cleanup pass
2026-01-30 Fix datastore.js
2026-01-30 Add some JS testing
2026-01-30 More cleanup
2026-02-01 Make the cell parsing testable
2026-02-01 Draft some firmware flashing docs
2026-02-19 Add some more cell error cases, and update flashing firmware docs
2026-03-02 switch R35 to JLC basic on Main and Jr boards
2026-05-11 Jr +
2026-05-11 Calibration fixes
2026-05-11 Initial poking at a zephyr rewrite
2026-05-11 Start spooling up O2 logic
2026-05-11 Ensure config changes are linted for validity
2026-05-11 Set up error handling
2026-05-11 Cell initial work
2026-05-11 Power management
2026-05-11 Initial bringup
2026-05-11 Add assertion for version check
2026-05-11 Fix some startup errors
2026-05-11 Fix ADC and logs
2026-05-11 Initial CAN impl
2026-05-11 Quality pass
2026-05-12 Comment pass
2026-05-12 PPO2 control logic
2026-05-12 Wiring up and tidy up pass
2026-05-12 WDT timing, pwr management
2026-05-12 Start building out integration testing
2026-05-12 Change the bus timing to decouple the timing from the cells
2026-05-13 Polish off the integration testing framework build
2026-05-13 Fix broken power build
2026-05-13 Add histogram for errors and expose cell data over DIDs
2026-05-13 Initial MCUboot add
2026-05-14 Add testing of corruption detection
2026-05-14 UDS update
2026-05-14 Factory image logic and power on self test
2026-05-14 Fix RTT to smoothly transition from boot to app
2026-05-14 Factory rollback capabilities
2026-05-14 Improve performance of integration tests
2026-05-14 Start SMF migration
2026-05-14 Port the rest of everything to SMF
2026-05-14 Change to a shared memory shim, vastly improve test speed
2026-05-14 Build out flash log system
2026-05-14 Clear out old shim socket
2026-05-15 Mem optimisation pass
2026-05-15 Coverage tracking
2026-05-15 Esnure range checks of cell calibration
2026-05-18 Try and get flash log working
2026-06-23 updates from looking at board in updated kicad
2026-06-23 Add some HIL testing changes
2026-06-23 Add additional configurations
2026-06-23 Ensure we put the solid cells into the right state on startup
2026-06-23 Add enhanced error checkin in the HAL
2026-06-23 Ensure analog builds
2026-06-24 remove testing instrumentation
2026-06-24 Get OTA passing basic tests
2026-06-24 Get cell pinout right
2026-06-24 Capture voltages as part of testing manifest
2026-06-24 Fix large flash issue
2026-06-25 Flash fix for flogging on filled startup
2026-06-25 Fix shutdown
2026-06-25 Use correct cal mode when requested
2026-06-25 Fix 3 vs 4 byte addressing
2026-06-25 Fix cal requirements for flush and add UDS mass erase
2026-06-25 Fix crash on calibrate due to OOM
2026-06-25 Fix UDS temp overrides not taking effect
2026-06-26 Fix cell 2 not sharing ADC correctly under zephyr
2026-06-26 Fix battery changing
2026-06-26 Fixes arising from test cases
2026-06-27 Fix bugs in OTA pathway
2026-06-27 Strip unused diagnostics, fix log, fix some sad counters
2026-06-27 Fix ADC driver to serialise properly
2026-06-28 Get solenoids firing
2026-06-29 Add sidewinder build
2026-06-29 Add supoort for broadcast mode on cells and pyro/diveO2 autodetection. Also let UDS dialogs preempt log messages
2026-06-29 Fix flakyness in isotp subsystem
2026-06-29 Fix DiveO2 cell issues
2026-06-29 Initial LF structuring
2026-06-30 Fixs from doing a full variant coverage campaign
